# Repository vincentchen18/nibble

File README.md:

# Nibble

## Overview

Nibble is a tiny 4-bit computer made from nothing but 74HC logic chips. No microcontroller, no Arduino, no EEPROM, just 11 chips and a whole lot of diodes. It's called Nibble because 4 bits is a nibble, and I thought that was funny. :DDD

The fun part is that the program is stored in a grid of 112 diodes, so instead of uploading code you "flash" it with a soldering iron. Yes, really. To change the program you desolder diodes. No, I will not be adding a USB port for programming. :C

This project was built for week 5 of Hack Club's [Half Life YSWS](https://halflife.hackclub.com) program.

## Schematics

Above is the final schematic for Nibble, made in KiCad. It contains a 74HC161 program counter, three 74HC138 decoders, a 74HC86 + 74HC283 ALU, a 74HC157 mux, two 74HC377 registers, a 74HC00 for the jump logic, a 555 timer for the clock, a 16 × 7 diode ROM, 4 LEDs and a USB-C port for power.

The PCB layout is above. yeah idk what else to say, but the right side was basically just a wiry mess.

## Features

- 4-bit CPU made from 11 logic chips
- 8 instructions (listed below)
- 16-step programs stored in diodes (diode = 0, no diode = 1)
- Carry flag, so it can do loops and conditionals (it's basically turing complete if you squint. very hard.)
- 4 LEDs to show the output
- ~2 Hz clock so you can actually watch it think
- Empty ROM rows read as `HLT`, so it can't run off into nothing
- Reset button + auto reset on power up
- USB-C powered

### Instruction set

| Opcode | Instruction | What it does |
|---|---|---|
| `000` | `ADD n` | acc = acc + n (same as 010) |
| `001` | `LDI n` | acc = n |
| `010` | `ADD n` | acc = acc + n, carry flag updates |
| `011` | `SUB n` | acc = acc − n, carry = 1 if there was no borrow |
| `100` | `OUT` | shows acc on the LEDs |
| `101` | `JMP n` | jump to row n |
| `110` | `JC n` | jump to row n, but only if carry = 1 |
| `111` | `HLT` | stops the clock |

Please note that `LDI` also updates the carry flag, so don't use `JC` straight after an `LDI` (it will not do what you want :C)

## Firmware

There is no code. The firmware is literally which diodes you solder. Put a diode wherever you want a 0.

The demo program counts from 0 to 15 on the LEDs and then stops:

| Row | Instruction | Bits | Diodes |
|---|---|---|---|
| 0 | `LDI 0` | `001 0000` | 6 |
| 1 | `OUT` | `100 1111` | 2 |
| 2 | `ADD 1` | `010 0001` | 5 |
| 3 | `JC 5` | `110 0101` | 3 |
| 4 | `JMP 1` | `101 0001` | 4 |
| 5 to 15 | `HLT` | `111 1111` | 0 |

## Hardware & Assembly

Basically, you solder all the chips, resistors, caps, LEDs, the button and the USB-C port like a normal PCB. Then for the ROM, you only solder the diodes that your program needs, all facing the same way (bar towards the row, follow the silkscreen).

Plug it into USB-C, press reset, and watch it count. :33

Some things to note:

- The 5.1k resistors next to the USB-C port are needed or chargers won't give it power.
- If you want a different program, desolder and resolder the diodes. Good luck.

## AI Usage

No AI used in this project.

## Bill of Materials
 
| Item | Purpose | Qty | Price | Source |
|---|---|---|---|---|
| Custom PCB 100×100mm, 2-layer (incl. US$7.60 shipping) | Main board | 5 | US$11.60 | [JLCPCB](https://jlcpcb.com) |
| TI SN74HC161DR SOIC-16 | Program counter | 5 (1 needed) | US$2.56 | [LCSC](https://www.lcsc.com/product-detail/C6824.html?s_z=n_q_C6824&globalKeyword=C6824) |
| Nexperia 74HC138D SOIC-16 | Row decoders + opcode decoder | 5 (3 needed) | US$1.00 | [LCSC](https://www.lcsc.com/product-detail/C5602.html?s_z=n_q_C5602&globalKeyword=C5602) |
| Nexperia 74HC86D SOIC-14 | XOR (for subtracting) | 5 (1 needed) | US$0.71 | [LCSC](https://www.lcsc.com/product-detail/C5955.html?s_z=n_q_C5955&globalKeyword=C5955) |
| TI CD74HC283M96 SOIC-16 | 4-bit adder | 1 | US$0.75 | [LCSC](https://www.lcsc.com/product-detail/C543032.html?s_z=n_q_C543032&globalKeyword=C543032) |
| Nexperia 74HC157D SOIC-16 | Mux | 5 (1 needed) | US$1.85 | [LCSC](https://www.lcsc.com/product-detail/C5609.html?s_z=n_q_C5609&globalKeyword=C5609) |
| Nexperia 74HC377D SOIC-20W | Accumulator + output register | 5 (2 needed) | US$3.85 | [LCSC](https://www.lcsc.com/product-detail/C5639.html?s_z=n_q_C5639&globalKeyword=C5639) |
| Nexperia 74HC00D SOIC-14 | Jump logic | 5 (1 needed) | US$0.60 | [LCSC](https://www.lcsc.com/product-detail/C5586.html?s_z=n_q_C5586&globalKeyword=C5586) |
| TI NE555DR SOIC-8 | Clock | 5 (1 needed) | US$0.55 | [LCSC](https://www.lcsc.com/product-detail/C7593.html?s_z=n_q_C7593&globalKeyword=C7593) |
| 1N4148W SOD-123 | Diode ROM | 50 (20 needed for the demo) | US$0.60 | [LCSC](https://www.lcsc.com/product-detail/C81598.html?s_z=n_q_C81598&globalKeyword=C81598) |
| KT-0603R red LED 0603 | Output | 1 pack (4 needed) | US$0.77 | [LCSC](https://www.lcsc.com/product-detail/C2286.html?s_z=n_q_C2286&globalKeyword=C2286) |
| 10k 0603 resistor | ROM pull-ups + reset | 100 (8 needed) | US$0.22 | [LCSC](https://www.lcsc.com/product-detail/C25804.html?s_z=n_q_C25804&globalKeyword=C25804) |
| 1k 0603 resistor | LEDs + clock | 100 (5 needed) | US$0.17 | [LCSC](https://www.lcsc.com/product-detail/C21190.html?s_z=n_q_C21190&globalKeyword=C21190) |
| 33k 0603 resistor | Clock | 100 (1 needed) | US$0.21 | [LCSC](https://www.lcsc.com/product-detail/C4216.html?s_z=n_q_C4216&globalKeyword=C4216) |
| 5.1k 0603 resistor | USB-C CC | 100 (2 needed) | US$0.16 | [LCSC](https://www.lcsc.com/product-detail/C23186.html?s_z=n_q_C23186&globalKeyword=C23186) |
| 100nF 0603 capacitor | Decoupling (1 per chip) | 1 pack (11 needed) | US$0.72 | [LCSC](https://www.lcsc.com/product-detail/C1591.html?s_z=n_q_C1591&globalKeyword=C1591) |
| 10uF 0805 capacitor | Clock, power-on reset, bulk | 1 pack (3 needed) | US$0.72 | [LCSC](https://www.lcsc.com/product-detail/C15850.html?s_z=n_q_C15850&globalKeyword=C15850) |
| SHOU HAN TS665CJ 6×6mm THT tactile switch | Reset | 1 pack (1 needed) | US$0.94 | [LCSC](https://www.lcsc.com/product-detail/C393938.html?s_z=n_q_C393938&globalKeyword=C393938) |
| USB-C 6-pin power-only receptacle | Power | 5 (1 needed) | US$0.22 | [LCSC](https://www.lcsc.com/product-detail/C18357552.html?s_z=n_q_C18357552&globalKeyword=C18357552) |
| **Total** | | | **US$28.20 + LCSC shipping** | |

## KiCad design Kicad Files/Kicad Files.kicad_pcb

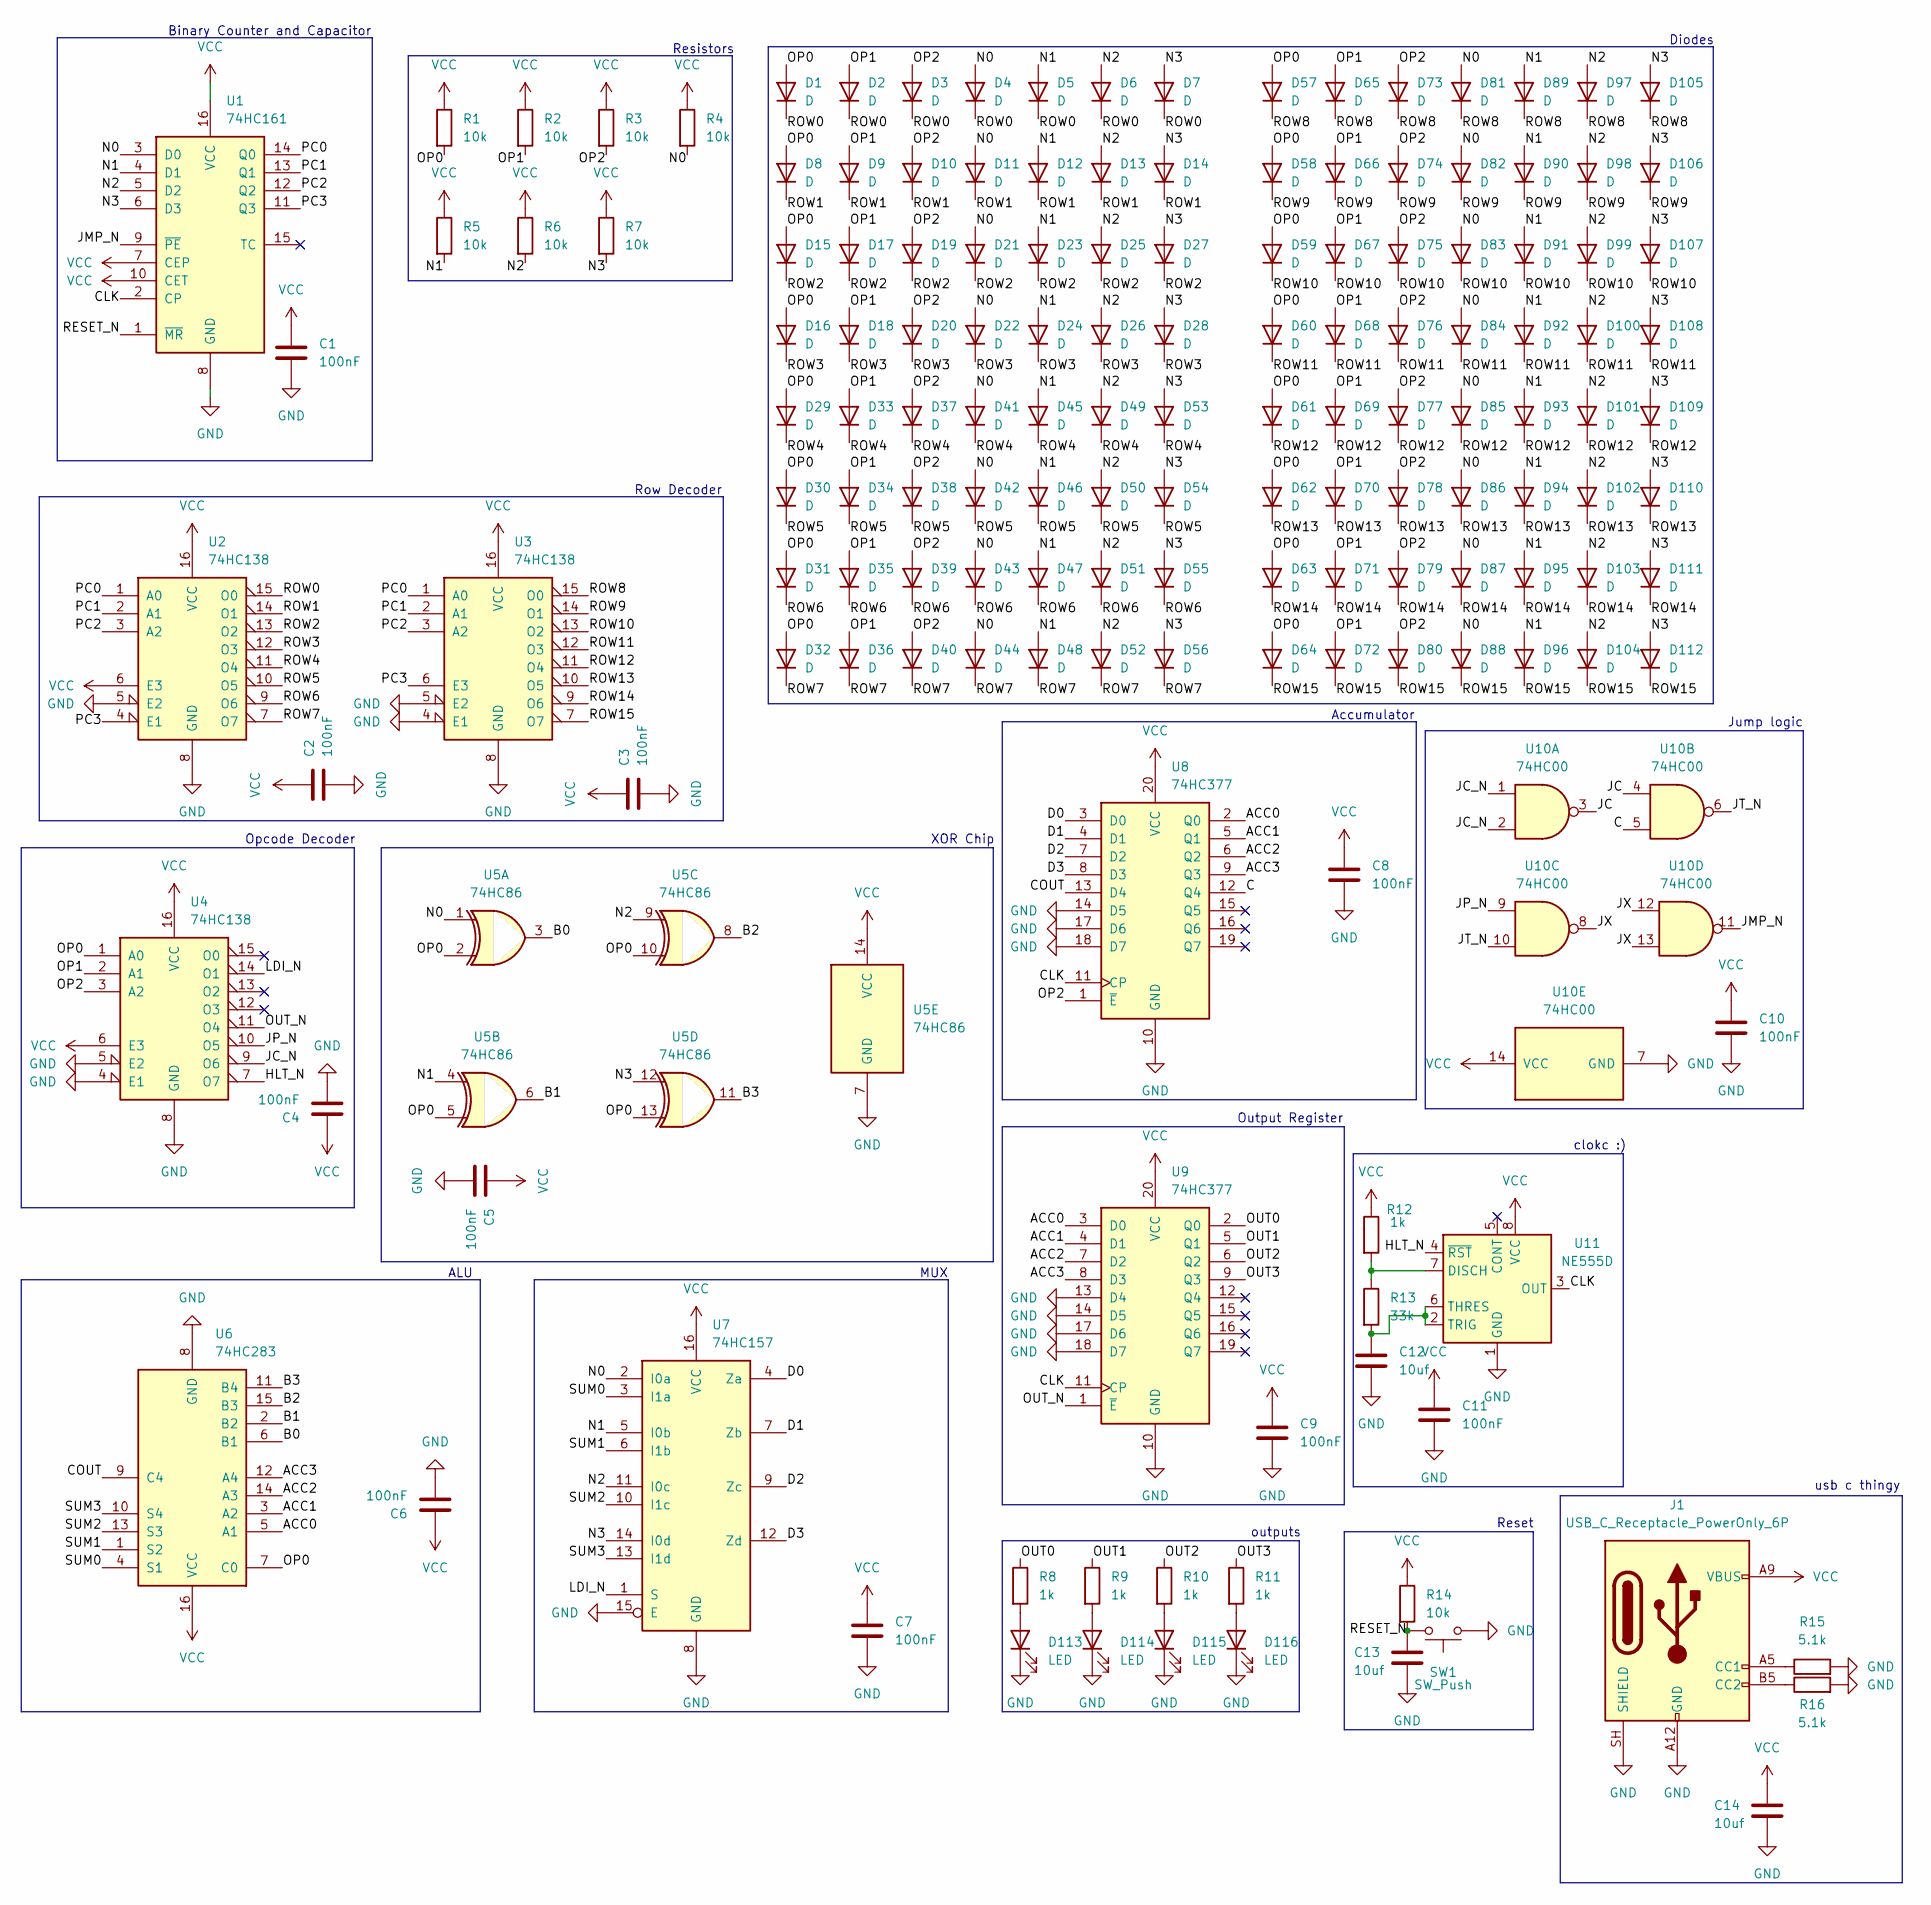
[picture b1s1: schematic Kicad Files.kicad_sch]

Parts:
C1, C2, C3, C4, C5, C6, C7, C8, C9, C10, C11: 100nF; C_0603_1608Metric
C12, C13, C14: 10uf; C_0805_2012Metric
D1, D2, D3, D4, D5, D6, D7, D8, D9, D10, D11, D12, D13, D14, D15, D16, D17, D18, D19, D20, D21, D22, D23, D24, D25, D26, D27, D28, D29, D30, D31, D32, D33, D34, D35, D36, D37, D38, D39, D40, D41, D42, D43, D44, D45, D46, D47, D48, D49, D50, D51, D52, D53, D54, D55, D56, D57, D58, D59, D60, D61, D62, D63, D64, D65, D66, D67, D68, D69, D70, D71, D72, D73, D74, D75, D76, D77, D78, D79, D80, D81, D82, D83, D84, D85, D86, D87, D88, D89, D90, D91, D92, D93, D94, D95, D96, D97, D98, D99, D100, D101, D102, D103, D104, D105, D106, D107, D108, D109, D110, D111, D112: D; D_SOD-123
D113, D114, D115, D116: LED; LED_0603_1608Metric
J1: USB_C_Receptacle_PowerOnly_6P; USB_C_Receptacle_GCT_USB4125-xx-x_6P_TopMnt_Horizontal
R1, R2, R3, R4, R5, R6, R7, R14: 10k; R_0603_1608Metric
R8, R9, R10, R11, R12: 1k; R_0603_1608Metric
R13: 33k; R_0603_1608Metric
R15, R16: 5.1k; R_0603_1608Metric
SW1: SW_Push; SW_PUSH_6mm
U1: 74HC161; SOIC-16_3.9x9.9mm_P1.27mm
U2, U3, U4: 74HC138; SOIC-16_3.9x9.9mm_P1.27mm
U5: 74HC86; SOIC-14_3.9x8.7mm_P1.27mm
U6: 74HC283; SOIC-16_3.9x9.9mm_P1.27mm
U7: 74HC157; SOIC-16_3.9x9.9mm_P1.27mm
U8, U9: 74HC377; SOIC-20W_7.5x12.8mm_P1.27mm
U10: 74HC00; SOIC-14_3.9x8.7mm_P1.27mm
U11: NE555D; SOIC-8_3.9x4.9mm_P1.27mm

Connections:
/ACC0: U6.5 (A1), U8.2 (Q0), U9.3 (D0)
/ACC1: U6.3 (A2), U8.5 (Q1), U9.4 (D1)
/ACC2: U6.14 (A3), U8.6 (Q2), U9.7 (D2)
/ACC3: U6.12 (A4), U8.9 (Q3), U9.8 (D3)
/B0: U5.3, U6.6 (B1)
/B1: U5.6, U6.2 (B2)
/B2: U5.8, U6.15 (B3)
/B3: U5.11, U6.11 (B4)
/C: U8.12 (Q4), U10.5
/CLK: U1.2 (CP), U8.11 (CP), U9.11 (CP), U11.3 (OUT)
/COUT: U6.9 (C4), U8.13 (D4)
/D0: U7.4 (Za), U8.3 (D0)
/D1: U7.7 (Zb), U8.4 (D1)
/D2: U7.9 (Zc), U8.7 (D2)
/D3: U7.12 (Zd), U8.8 (D3)
/HLT_N: U4.7 (O7), U11.4 (~RST)
/JC: U10.3, U10.4
/JC_N: U4.9 (O6), U10.1, U10.2
/JMP_N: U1.9 (~PE), U10.11
/JP_N: U4.10 (O5), U10.9
/JT_N: U10.6, U10.10
/JX: U10.8, U10.12, U10.13
/LDI_N: U4.14 (O1), U7.1 (S)
/N0: D4.2 (A), D11.2 (A), D21.2 (A), D22.2 (A), D41.2 (A), D42.2 (A), D43.2 (A), D44.2 (A), D81.2 (A), D82.2 (A), D83.2 (A), D84.2 (A), D85.2 (A), D86.2 (A), D87.2 (A), D88.2 (A), R4.2, U1.3 (D0), U5.1, U7.2 (I0a)
/N1: D5.2 (A), D12.2 (A), D23.2 (A), D24.2 (A), D45.2 (A), D46.2 (A), D47.2 (A), D48.2 (A), D89.2 (A), D90.2 (A), D91.2 (A), D92.2 (A), D93.2 (A), D94.2 (A), D95.2 (A), D96.2 (A), R5.2, U1.4 (D1), U5.4, U7.5 (I0b)
/N2: D6.2 (A), D13.2 (A), D25.2 (A), D26.2 (A), D49.2 (A), D50.2 (A), D51.2 (A), D52.2 (A), D97.2 (A), D98.2 (A), D99.2 (A), D100.2 (A), D101.2 (A), D102.2 (A), D103.2 (A), D104.2 (A), R6.2, U1.5 (D2), U5.9, U7.11 (I0c)
/N3: D7.2 (A), D14.2 (A), D27.2 (A), D28.2 (A), D53.2 (A), D54.2 (A), D55.2 (A), D56.2 (A), D105.2 (A), D106.2 (A), D107.2 (A), D108.2 (A), D109.2 (A), D110.2 (A), D111.2 (A), D112.2 (A), R7.2, U1.6 (D3), U5.12, U7.14 (I0d)
/OP0: D1.2 (A), D8.2 (A), D15.2 (A), D16.2 (A), D29.2 (A), D30.2 (A), D31.2 (A), D32.2 (A), D57.2 (A), D58.2 (A), D59.2 (A), D60.2 (A), D61.2 (A), D62.2 (A), D63.2 (A), D64.2 (A), R1.2, U4.1 (A0), U5.2, U5.5, U5.10, U5.13, U6.7 (C0)
/OP1: D2.2 (A), D9.2 (A), D17.2 (A), D18.2 (A), D33.2 (A), D34.2 (A), D35.2 (A), D36.2 (A), D65.2 (A), D66.2 (A), D67.2 (A), D68.2 (A), D69.2 (A), D70.2 (A), D71.2 (A), D72.2 (A), R2.2, U4.2 (A1)
/OP2: D3.2 (A), D10.2 (A), D19.2 (A), D20.2 (A), D37.2 (A), D38.2 (A), D39.2 (A), D40.2 (A), D73.2 (A), D74.2 (A), D75.2 (A), D76.2 (A), D77.2 (A), D78.2 (A), D79.2 (A), D80.2 (A), R3.2, U4.3 (A2), U8.1 (~E)
/OUT0: R8.1, U9.2 (Q0)
/OUT1: R9.1, U9.5 (Q1)
/OUT2: R10.1, U9.6 (Q2)
/OUT3: R11.1, U9.9 (Q3)
/OUT_N: U4.11 (O4), U9.1 (~E)
/PC0: U1.14 (Q0), U2.1 (A0), U3.1 (A0)
/PC1: U1.13 (Q1), U2.2 (A1), U3.2 (A1)
/PC2: U1.12 (Q2), U2.3 (A2), U3.3 (A2)
/PC3: U1.11 (Q3), U2.4 (E1), U3.6 (E3)
/RESET_N: C13.1, R14.2, SW1.2, U1.1 (~MR)
/ROW0: D1.1 (K), D2.1 (K), D3.1 (K), D4.1 (K), D5.1 (K), D6.1 (K), D7.1 (K), U2.15 (O0)
/ROW1: D8.1 (K), D9.1 (K), D10.1 (K), D11.1 (K), D12.1 (K), D13.1 (K), D14.1 (K), U2.14 (O1)
/ROW2: D15.1 (K), D17.1 (K), D19.1 (K), D21.1 (K), D23.1 (K), D25.1 (K), D27.1 (K), U2.13 (O2)
/ROW3: D16.1 (K), D18.1 (K), D20.1 (K), D22.1 (K), D24.1 (K), D26.1 (K), D28.1 (K), U2.12 (O3)
/ROW4: D29.1 (K), D33.1 (K), D37.1 (K), D41.1 (K), D45.1 (K), D49.1 (K), D53.1 (K), U2.11 (O4)
/ROW5: D30.1 (K), D34.1 (K), D38.1 (K), D42.1 (K), D46.1 (K), D50.1 (K), D54.1 (K), U2.10 (O5)
/ROW6: D31.1 (K), D35.1 (K), D39.1 (K), D43.1 (K), D47.1 (K), D51.1 (K), D55.1 (K), U2.9 (O6)
/ROW7: D32.1 (K), D36.1 (K), D40.1 (K), D44.1 (K), D48.1 (K), D52.1 (K), D56.1 (K), U2.7 (O7)
/ROW8: D57.1 (K), D65.1 (K), D73.1 (K), D81.1 (K), D89.1 (K), D97.1 (K), D105.1 (K), U3.15 (O0)
/ROW9: D58.1 (K), D66.1 (K), D74.1 (K), D82.1 (K), D90.1 (K), D98.1 (K), D106.1 (K), U3.14 (O1)
/ROW10: D59.1 (K), D67.1 (K), D75.1 (K), D83.1 (K), D91.1 (K), D99.1 (K), D107.1 (K), U3.13 (O2)
/ROW11: D60.1 (K), D68.1 (K), D76.1 (K), D84.1 (K), D92.1 (K), D100.1 (K), D108.1 (K), U3.12 (O3)
/ROW12: D61.1 (K), D69.1 (K), D77.1 (K), D85.1 (K), D93.1 (K), D101.1 (K), D109.1 (K), U3.11 (O4)
/ROW13: D62.1 (K), D70.1 (K), D78.1 (K), D86.1 (K), D94.1 (K), D102.1 (K), D110.1 (K), U3.10 (O5)
/ROW14: D63.1 (K), D71.1 (K), D79.1 (K), D87.1 (K), D95.1 (K), D103.1 (K), D111.1 (K), U3.9 (O6)
/ROW15: D64.1 (K), D72.1 (K), D80.1 (K), D88.1 (K), D96.1 (K), D104.1 (K), D112.1 (K), U3.7 (O7)
/SUM0: U6.4 (S1), U7.3 (I1a)
/SUM1: U6.1 (S2), U7.6 (I1b)
/SUM2: U6.13 (S3), U7.10 (I1c)
/SUM3: U6.10 (S4), U7.13 (I1d)
GND: C1.2, C2.2, C3.2, C4.2, C5.2, C6.2, C7.2, C8.2, C9.2, C10.2, C11.2, C12.2, C13.2, C14.2, D113.1 (K), D114.1 (K), D115.1 (K), D116.1 (K), J1.A12 (GND), J1.B12 (GND), J1.SH (SHIELD), R15.2, R16.2, SW1.1, U1.8 (GND), U2.5 (E2), U2.8 (GND), U3.4 (E1), U3.5 (E2), U3.8 (GND), U4.4 (E1), U4.5 (E2), U4.8 (GND), U5.7 (GND), U6.8 (GND), U7.8 (GND), U7.15 (E), U8.10 (GND), U8.14 (D5), U8.17 (D6), U8.18 (D7), U9.10 (GND), U9.13 (D4), U9.14 (D5), U9.17 (D6), U9.18 (D7), U10.7 (GND), U11.1 (GND)
unnamed: D113.2 (A), R8.2
unnamed: D114.2 (A), R9.2
unnamed: D115.2 (A), R10.2
unnamed: D116.2 (A), R11.2
unnamed: J1.A5 (CC1), R15.1
unnamed: J1.B5 (CC2), R16.1
unnamed: R12.2, R13.1, U11.7 (DISCH)
unnamed: C12.1, R13.2, U11.2 (TRIG), U11.6 (THRES)
VCC: C1.1, C2.1, C3.1, C4.1, C5.1, C6.1, C7.1, C8.1, C9.1, C10.1, C11.1, C14.1, J1.A9 (VBUS), J1.B9 (VBUS), R1.1, R2.1, R3.1, R4.1, R5.1, R6.1, R7.1, R12.1, R14.1, U1.7 (CEP), U1.10 (CET), U1.16 (VCC), U2.6 (E3), U2.16 (VCC), U3.16 (VCC), U4.6 (E3), U4.16 (VCC), U5.14 (VCC), U6.16 (VCC), U7.16 (VCC), U8.20 (VCC), U9.20 (VCC), U10.14 (VCC), U11.8 (VCC)

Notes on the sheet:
Accumulator
Jump logic
Binary Counter and Capacitor
Reset
Diodes
usb c thingy
Resistors
Output Register
MUX
XOR Chip
outputs
clokc :)
Row Decoder
Opcode Decoder
ALU

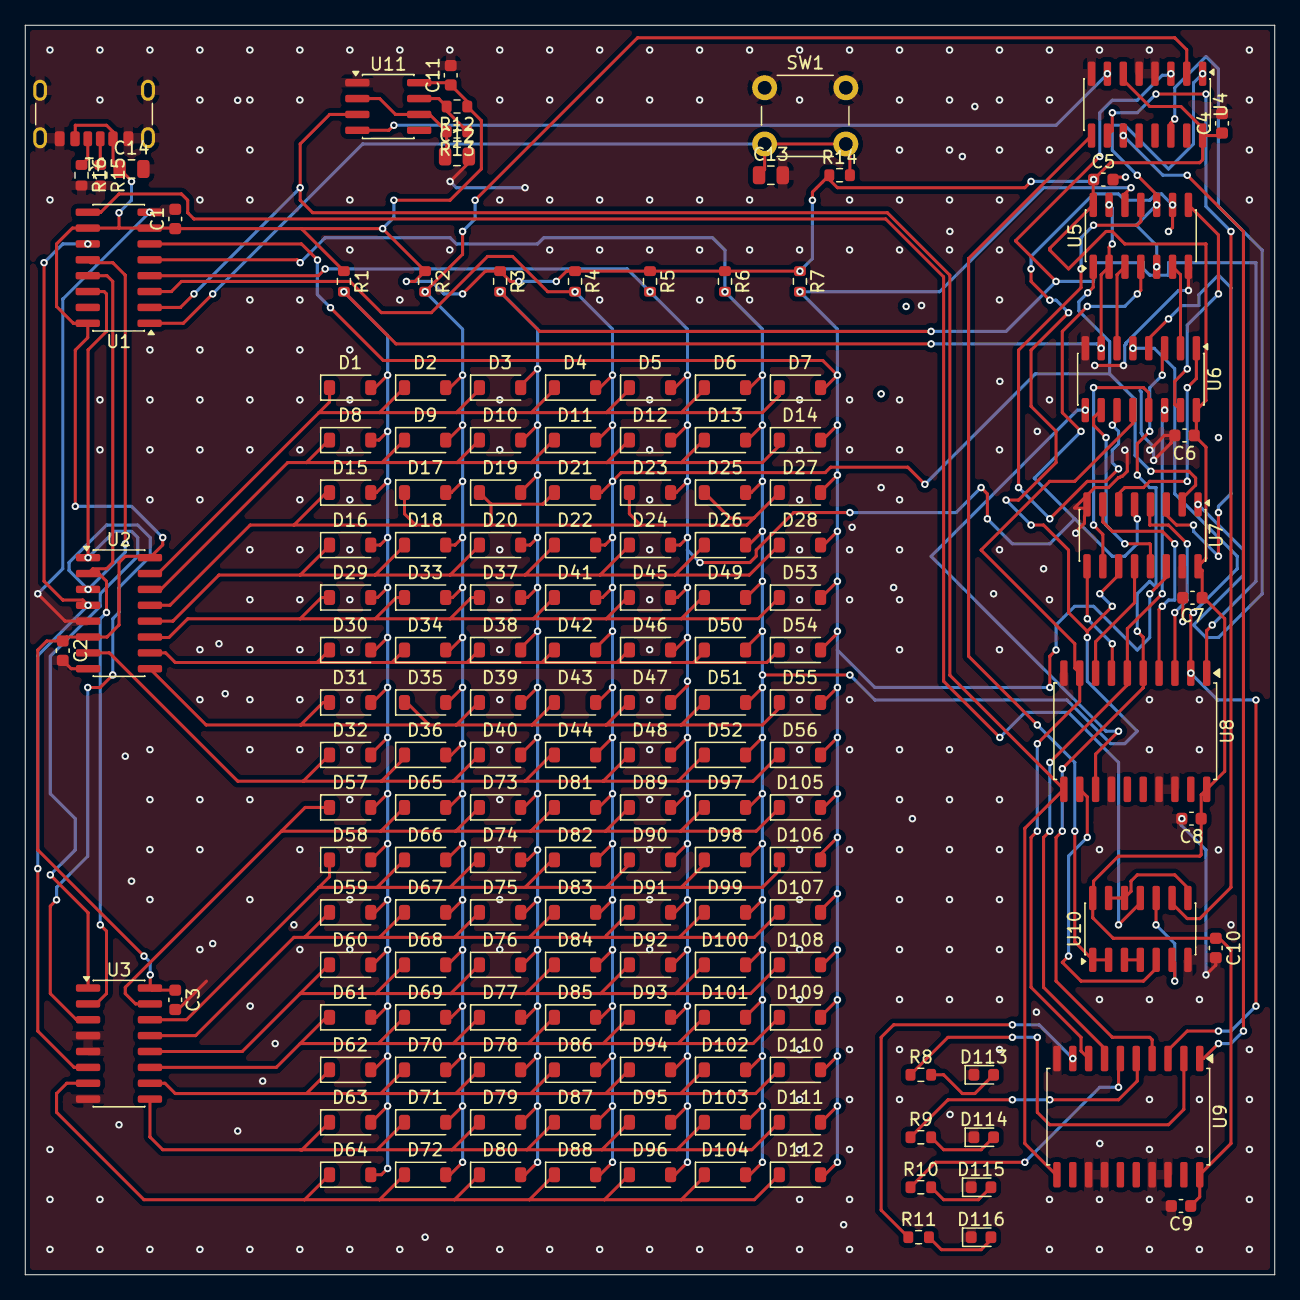
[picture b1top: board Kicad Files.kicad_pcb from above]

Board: 2 copper layers, 100.0 x 100.0 mm, 159 parts (0 on the bottom side), 70 nets.
